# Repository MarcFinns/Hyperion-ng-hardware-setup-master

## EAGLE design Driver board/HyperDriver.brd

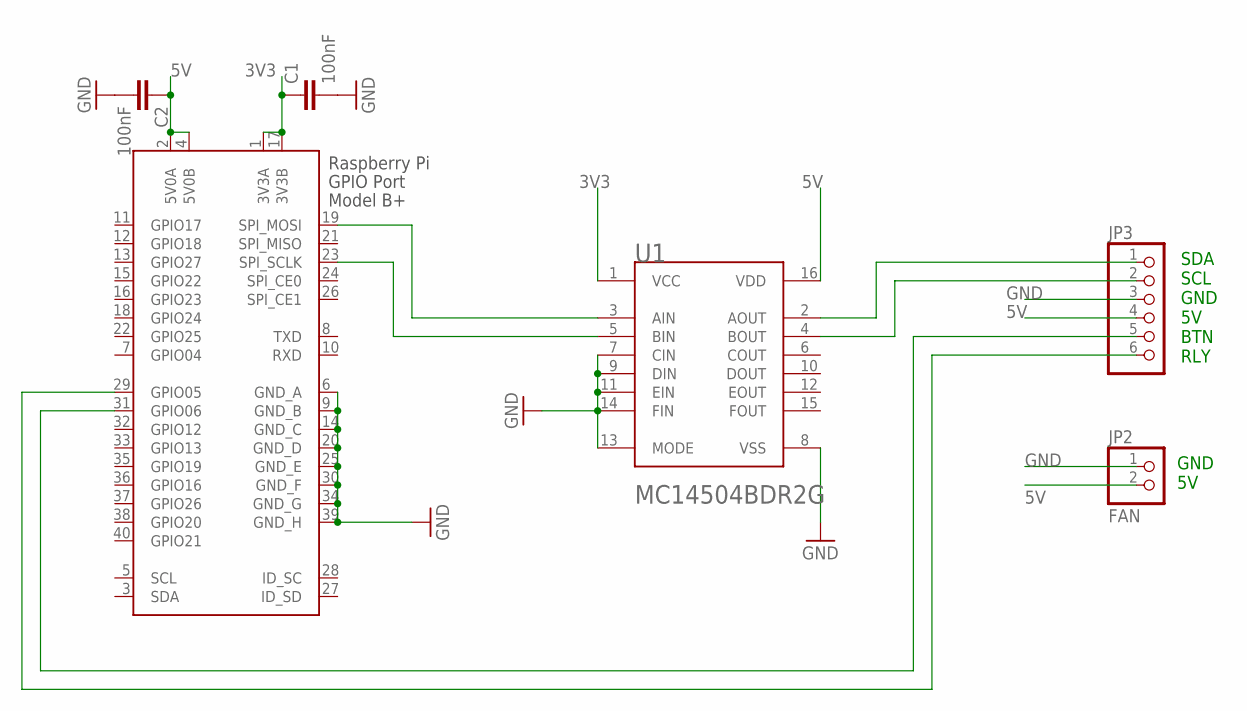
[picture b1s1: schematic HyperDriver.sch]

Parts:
C1, C2: 100nF; C0805K
JP2: FAN; 1X02
JP3: PINHD-1X6B; 1X06-BIG
U1: ON_SEMICONDUCTOR_MC14504BDR2GON_SEMICONDUCTOR_MC1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; ON_SEMICONDUCTOR_MC14504BDR2G_1
X1: RASPI_GPIO_B+#_PIN; RASPI_GPIO_B+_PIN

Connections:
3V3: C1.1, U1.1 (VCC), X1.1 (3V3A), X1.17 (3V3B)
5V: C2.1, JP2.2, JP3.4, U1.16 (VDD), X1.2 (5V0A), X1.4 (5V0B)
GND: C1.2, C2.2, JP2.1, JP3.3, U1.7 (CIN), U1.8 (VSS), U1.9 (DIN), U1.11 (EIN), U1.13 (MODE), U1.14 (FIN), X1.6 (GND_A), X1.9 (GND_B), X1.14 (GND_C), X1.20 (GND_D), X1.25 (GND_E), X1.30 (GND_F), X1.34 (GND_G), X1.39 (GND_H)
unnamed: JP3.1, U1.2 (AOUT)
unnamed: JP3.6, X1.29 (GPIO05)
unnamed: JP3.5, X1.31 (GPIO06)
unnamed: U1.3 (AIN), X1.19 (SPI_MOSI)
unnamed: U1.5 (BIN), X1.23 (SPI_SCLK)
unnamed: JP3.2, U1.4 (BOUT)

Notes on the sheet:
SDA SCL GND 5V BTN RLY
GND 5V

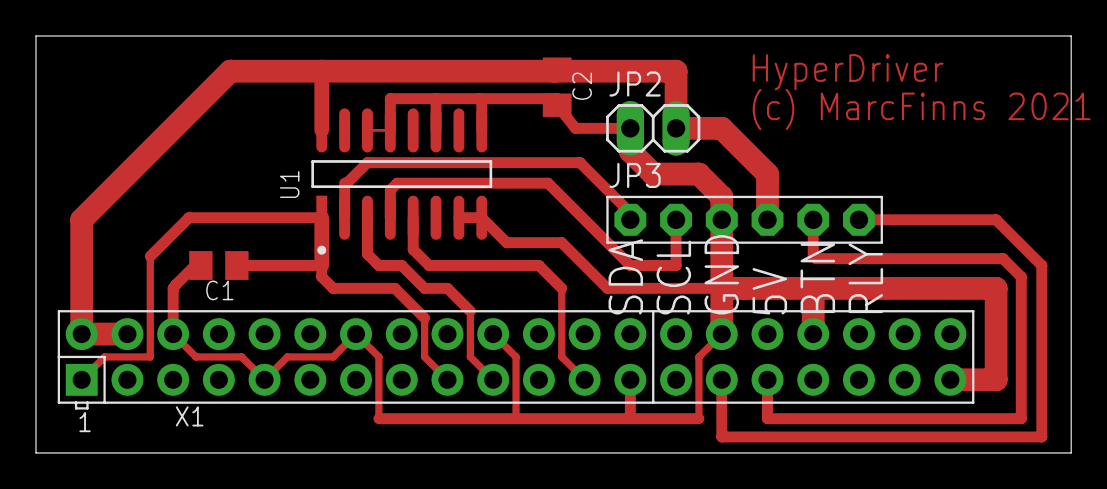
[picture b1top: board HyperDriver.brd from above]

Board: 2 copper layers, 57.5 x 23.2 mm, 6 parts (0 on the bottom side), 9 nets.

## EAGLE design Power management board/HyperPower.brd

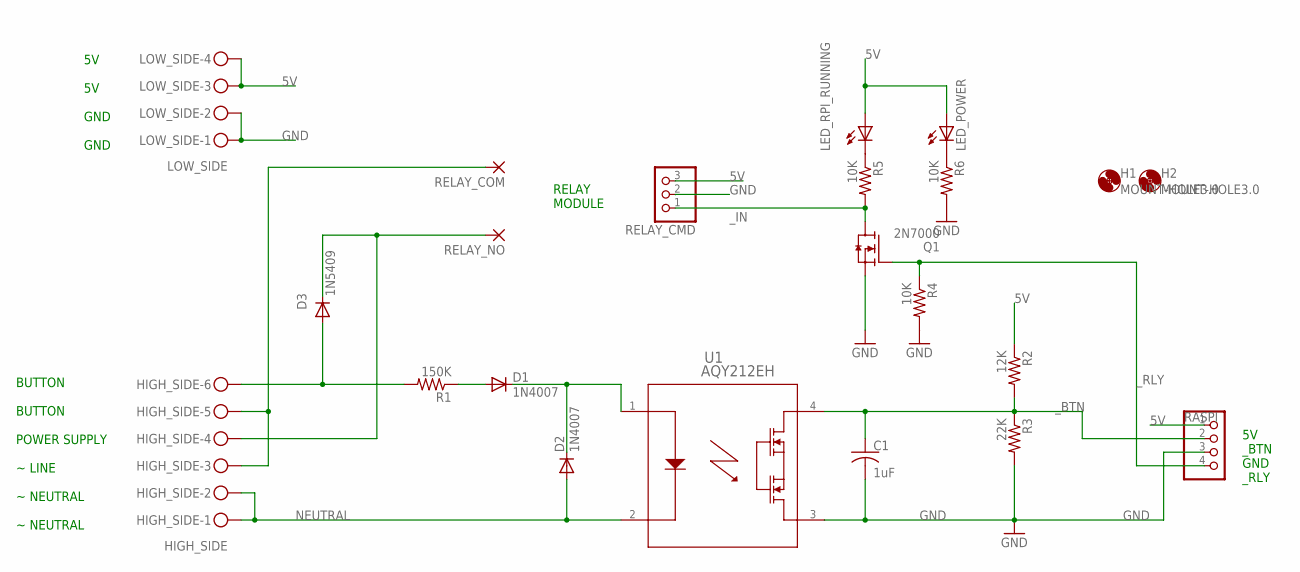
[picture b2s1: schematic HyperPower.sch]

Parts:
C1: 1uF; C025-040X050
D1, D2: 1N4007; DO41-10
D3: 1N5409; DO201-15
H1, H2: MOUNT-HOLE3.0; 3,0
HIGH_SIDE: HIGH_SIDE; MKDSN1,5/6-5,08
LED_POWER: LED_ELD260; LED_LD260
LED_RPI_RUNNING: LED_ELD260; LED_LD260
LOW_SIDE: LOW_SIDE; MKDSN1,5/4-5,08
Q1: 2N7000; TO92
R1: 150K; 0207/10
R2: 12K; 0207/10
R3: 22K; 0207/10
R4, R5, R6: 10K; 0207/10
RASPI: PINHD-1X4; 1X04
RELAY_CMD: PINHD-1X3; 1X03
RELAY_COM: 3,81/1,4
RELAY_NO: 3,81/1,4
U1: AQY212EH; PAN_AQY21-DIP4_PAN

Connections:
5V: LED_POWER.A, LED_RPI_RUNNING.A, LOW_SIDE.3, LOW_SIDE.4, R2.1, RASPI.1, RELAY_CMD.3
GND: C1.2, LOW_SIDE.1, LOW_SIDE.2, Q1.1 (S), R3.2, R4.2, R6.2, RASPI.3, RELAY_CMD.2, U1.3
unnamed: D1.C, D2.C, U1.1
unnamed: HIGH_SIDE.3, HIGH_SIDE.5, RELAY_COM.1
unnamed: D3.A, HIGH_SIDE.6, R1.2
unnamed: D3.C, HIGH_SIDE.4, RELAY_NO.1
unnamed: D1.A, R1.1
unnamed: LED_RPI_RUNNING.K (C), R5.1
unnamed: LED_POWER.K (C), R6.1
NEUTRAL: D2.A, HIGH_SIDE.1, HIGH_SIDE.2, U1.2
_BTN: C1.1, R2.2, R3.1, RASPI.2, U1.4
_IN: Q1.3 (D), R5.2, RELAY_CMD.1
_RLY: Q1.2 (G), R4.1, RASPI.4

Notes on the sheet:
BUTTON BUTTON POWER SUPPLY ~ LINE ~ NEUTRAL ~ NEUTRAL
5V 5V GND GND
5V _BTN GND _RLY
RELAY MODULE

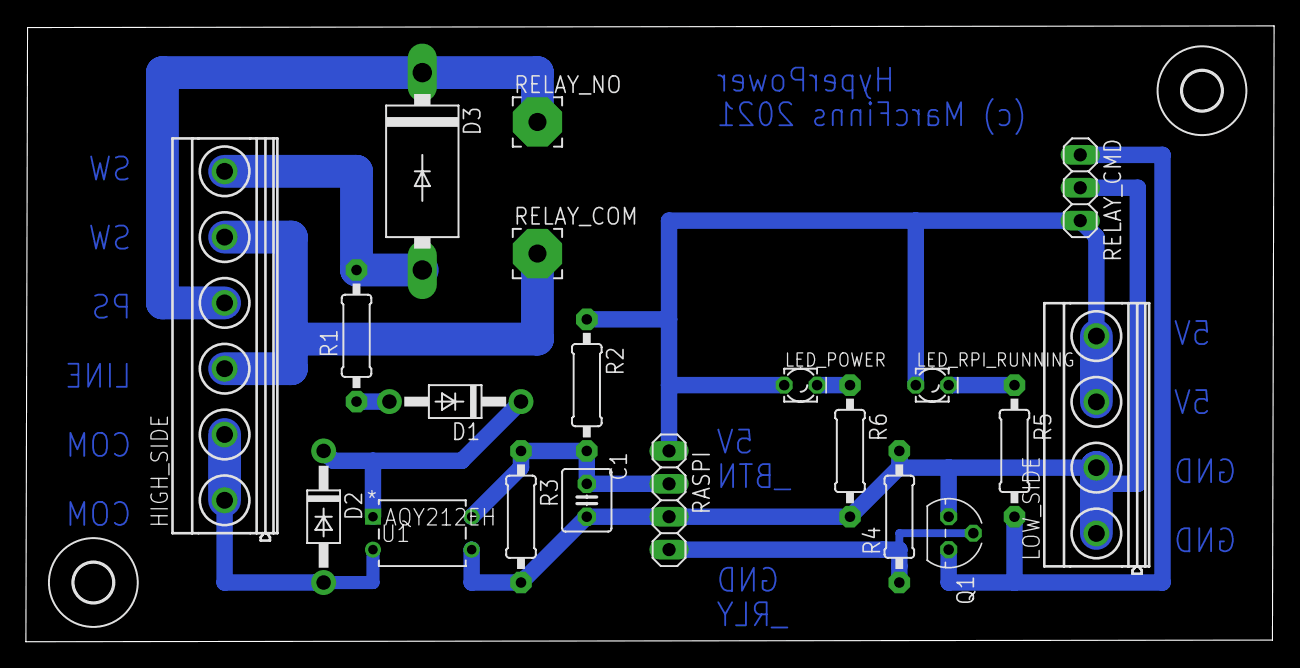
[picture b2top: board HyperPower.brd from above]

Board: 2 copper layers, 96.4 x 47.5 mm, 22 parts (0 on the bottom side), 13 nets.
